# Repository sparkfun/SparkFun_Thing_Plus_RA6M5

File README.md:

SparkFun Thing Plus - RA6M5
========================================

[*SparkFun Thing Plus - RA6M5 (WRL-24243)*](https://www.sparkfun.com/products/24243)

Clocking in at 200MHz, the RA6M5 is a high-performance microcontroller from [Renesas](https://www.renesas.com/) that is perfect for real-time applications. The [SparkFun Thing Plus - RA6M5](https://www.sparkfun.com/products/24243), is our latest [Thing Plus board](https://www.sparkfun.com/thing_plus) featuring the standard Qwiic connector, JST LiPo battery connector, 21 GPIO pins broken out in a Feather footprint, and status indicator LEDs. At the core is the RA6M5 microcontroller, a low-power Arm^®^ Cortex^®^-M33 processor with an available 512kB of SRAM and 2MB of Flash and an extensive list of peripheral capabilities. Additionally, we have included 16MB of QSPI Flash and an SD card slot on the board, so users won't have to worry about running out of memory space or data storage options.

The SparkFun RA6M5 Thing Plus also features Bluetooth® Low Energy connectivity, thanks to the provided DA14531MOD module *(also from Renesas)*. When actively transmitting, the DA14531MOD sips a mere 4mA and is capable of operating from a small coin-cell battery. The firmware provided on the module features Renesas' [SmartBond™ - CodeLess™ AT command](https://lpccs-docs.renesas.com/UM-140-DA145x-CodeLess/index.html) set. Therefore, users only need to send AT commands to configure a Bluetooth connection; without the need to reprogram the module.

**Note:**

- While the Thing Plus - RA6M5 does include some 5V tolerant pins, it is primarily a **3.3V** *logic-level* board.
- While the full capabilities of the RA6M5 support a broad range of features, only a limited set may be implemented, by default, in the [Renesas-Arduino core](https://github.com/arduino/ArduinoCore-renesas). However, the capabilities of the Thing Plus - RA6M5 should be comparable to the [Arduino Portenta C33](https://store.arduino.cc/collections/portenta-family/products/portenta-c33); with the exclusion of WiFi connectivity.

Documentation
--------------

* **[Hookup Guide (mkdocs)](http://docs.sparkfun.com/SparkFun_Thing_Plus_RA6M5/)** - The hookup guide for the Thing Plus - RA6M5 hosted by GitHub pages.<br>
   
* [SparkFun Graphical Datasheets](https://github.com/sparkfun/Graphical_Datasheets) - Graphical Datasheets for various SparkFun products.

*Need to download or print our hookup guide?*

* [Print *(Print to PDF)* from Single-Page View](http://docs.sparkfun.com/SparkFun_Thing_Plus_RA6M5/print_view)

Repository Contents
-------------------

* **[/docs](/docs/)** - Online documentation files
    * [assets](/docs/assets/) - Assets files
        * [board_files](/docs/assets/board_files/) - Files for the product design
            * [Eagle design files](/docs/assets/board_files/eagle_files.zip) (.zip)
            * [Schematic](/docs/assets/board_files/schematic.pdf) (.pdf)
            * [Dimensions](/docs/assets/board_files/dimensions.pdf) (.pdf)
            * [Graphical Datasheet](/docs/assets/board_files/graphical_datasheet.pdf) (.pdf)
        * [component_documentation](/docs/assets/component_documentation/) - Datasheets for hardware components
        * [img/hookup_guide/](/docs/assets/img/hookup_guide/) - Images for hookup guide documentation
* **[/Hardware](/Hardware/)** - Eagle design files (.brd, .sch)
  * **[/Production](/Production/)** - Production files

Product Variants
----------------

* [WRL-24243](https://www.sparkfun.com/products/24243)- v1.0, Initial Release

Version History
---------------

* [v10](https://github.com/sparkfun/SparkFun_Thing_Plus_RA6M5/releases/tag/v10) - Initial Release

License Information
-------------------

This product is ***open source***!

Please review the [`LICENSE.md`](./LICENSE.md) file for license information.

If you have any questions or concerns about licensing, please contact technical support on our [SparkFun forums](https://forum.sparkfun.com/viewforum.php?f=152).

Distributed as-is; no warranty is given.

- Your friends at SparkFun.

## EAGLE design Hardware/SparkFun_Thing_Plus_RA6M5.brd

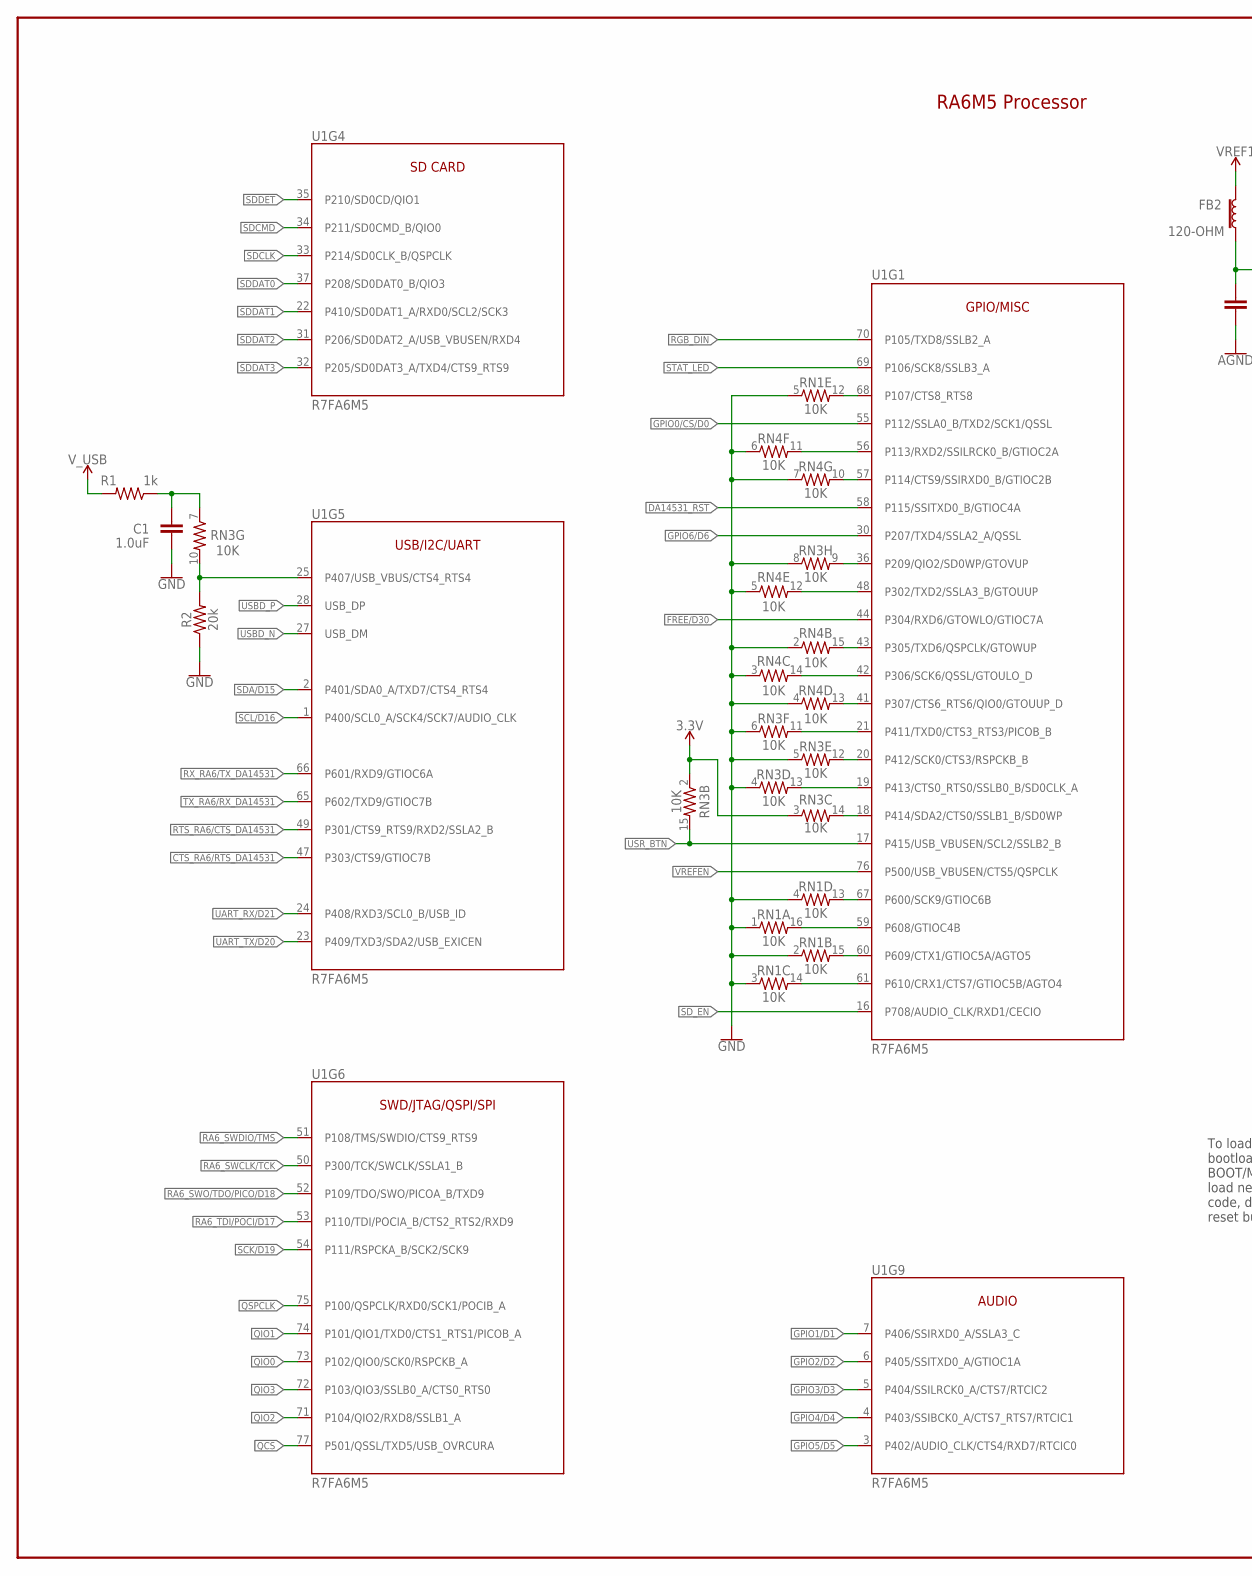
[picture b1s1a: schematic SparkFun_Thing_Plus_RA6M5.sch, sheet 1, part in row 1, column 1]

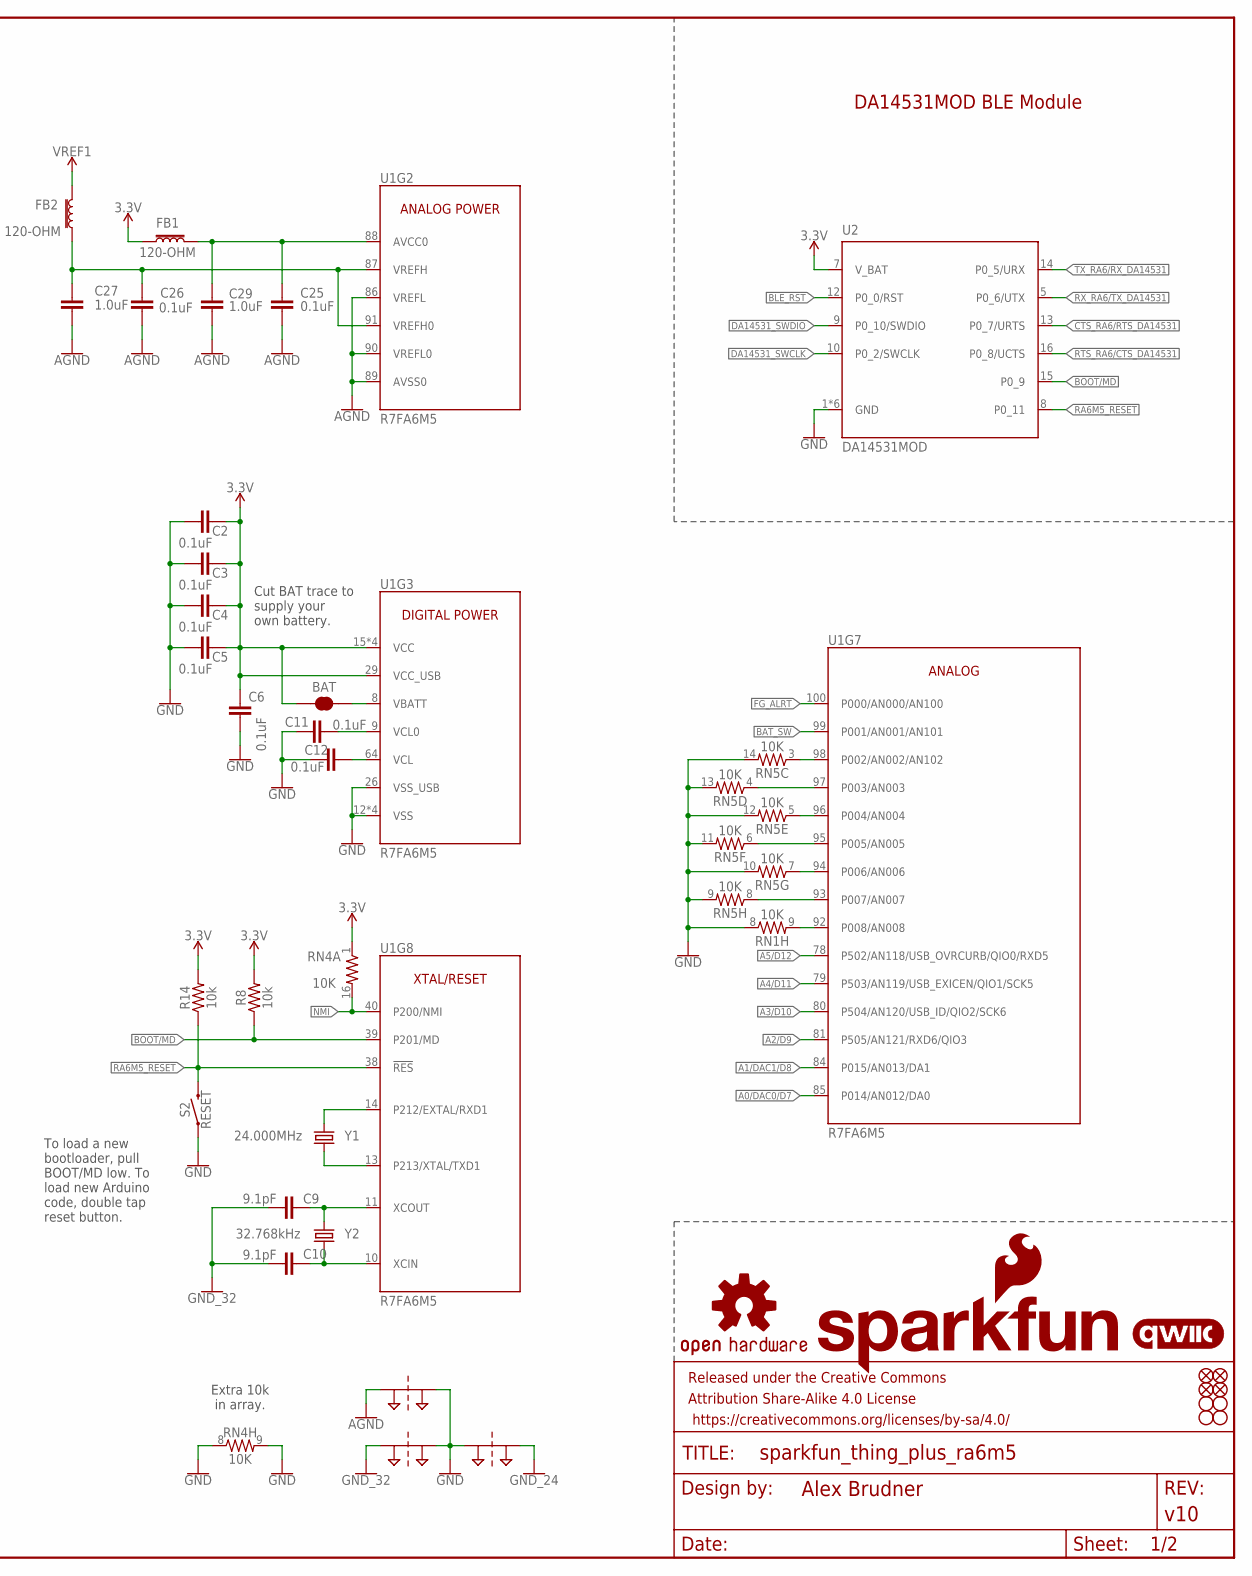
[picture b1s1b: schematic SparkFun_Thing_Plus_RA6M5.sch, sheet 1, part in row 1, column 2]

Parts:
BAT: JUMPER-SMT_2_NC_TRACE_SILK; SMT-JUMPER_2_NC_TRACE_SILK
C1, C27, C29: 1.0uF; 0402-TIGHT
C2, C3, C4, C5, C6, C11, C12, C25, C26: 0.1uF; 0402-TIGHT
C9, C10: 9.1pF; 0402-TIGHT
FB1, FB2: 120-OHM; 0402-TIGHT
FD1, FD2, FD3, FD4: FIDUCIALUFIDUCIAL; FIDUCIAL-MICRO
FRAME1: FRAME-LEDGER; CREATIVE_COMMONS
H1, H2, H3, H4: STAND-OFFTIGHT; STAND-OFF-TIGHT
LOGO1: OSHW-LOGOMINI; OSHW-LOGO-MINI
LOGO2: SFE_LOGO_NAME_FLAME.1_INCH; SFE_LOGO_NAME_FLAME_.1
LOGO3: QWIIC_LOGO_4MM; QWIIC_4MM
R1: 1k; 0402-TIGHT
R2: 20k; 0402-TIGHT
R8, R14: 10k; 0402-TIGHT
RN1, RN3, RN4, RN5: 10K; 2506_AR
S2: RESET; TACTILE_SWITCH_SMD_4.6X2.8MM
SUPPLYTIE1, SUPPLYTIE2, SUPPLYTIE3: 2PT_GND_TIESMALL; 2PT_GND_TIE_SMALL
U1: R7FA6M5; P-LQFP100-14X14-0.50
U2: DA14531MOD
Y1: 24.000MHz; 4-SMD,32X25
Y2: 32.768kHz; CRYSTAL-SMD-3.2X1.5MM

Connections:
3.3V: BAT.1, C2.1, C3.1, C4.1, C5.1, C6.1, FB1.1, R8.2, R14.2, RN3.2 (1), RN3.3 (1), RN4.1, U1.15 (VCC), U1.29 (VCC_USB), U1.46 (VCC), U1.62 (VCC), U1.82 (VCC), U2.7 (V_BAT); also elsewhere on the board
!CTS_RA6/RTS_DA14531!: U1.47 (P303/CTS9/GTIOC7B), U2.13 (P0_7/URTS); also elsewhere on the board
!DA14531_RST!: U1.58 (P115/SSITXD0_B/GTIOC4A); also elsewhere on the board
!FG_ALRT!: U1.100 (P000/AN000/AN100); also elsewhere on the board
!NMI!: RN4.16 (2), U1.40 (P200/NMI); also elsewhere on the board
!QCS!: U1.77 (P501/QSSL/TXD5/USB_OVRCURA); also elsewhere on the board
!RA6M5_RESET!: R14.1, S2.3 (2), S2.4 (2), U1.38 (!RES!), U2.8 (P0_11); also elsewhere on the board
!RTS_RA6/CTS_DA14531!: U1.49 (P301/CTS9_RTS9/RXD2/SSLA2_B), U2.16 (P0_8/UCTS); also elsewhere on the board
!SD_EN!: U1.16 (P708/AUDIO_CLK/RXD1/CECIO); also elsewhere on the board
!USR_BTN!: RN3.15 (2), U1.17 (P415/USB_VBUSEN/SCL2/SSLB2_B); also elsewhere on the board
A0/DAC0/D7: U1.85 (P014/AN012/DA0); also elsewhere on the board
A1/DAC1/D8: U1.84 (P015/AN013/DA1); also elsewhere on the board
A2/D9: U1.81 (P505/AN121/RXD6/QIO3); also elsewhere on the board
A3/D10: U1.80 (P504/AN120/USB_ID/QIO2/SCK6); also elsewhere on the board
A4/D11: U1.79 (P503/AN119/USB_EXICEN/QIO1/SCK5); also elsewhere on the board
A5/D12: U1.78 (P502/AN118/USB_OVRCURB/QIO0/RXD5); also elsewhere on the board
AGND: C25.2, C26.2, C27.2, C29.2, SUPPLYTIE1.P$1, U1.86 (VREFL), U1.89 (AVSS0), U1.90 (VREFL0)
AVCC0: C25.1, C29.1, FB1.2, U1.88 (AVCC0); also elsewhere on the board
BAT_SW: U1.99 (P001/AN001/AN101); also elsewhere on the board
BLE_RST: U2.12 (P0_0/RST); also elsewhere on the board
BOOT/MD: R8.1, U1.39 (P201/MD), U2.15 (P0_9); also elsewhere on the board
DA14531_SWCLK: U2.10 (P0_2/SWCLK); also elsewhere on the board
DA14531_SWDIO: U2.9 (P0_10/SWDIO); also elsewhere on the board
EXTAL: U1.14 (P212/EXTAL/RXD1), Y1.1
FREE/D30: U1.44 (P304/RXD6/GTOWLO/GTIOC7A); also elsewhere on the board
GND: C1.1, C2.2, C3.2, C4.2, C5.2, C6.2, C11.2, C12.2, R2.1, RN1.1, RN1.2 (1), RN1.3 (1), RN1.4 (1), RN1.5 (1), RN1.8 (1), RN3.4 (1), RN3.5 (1), RN3.6 (1), RN3.8 (1), RN4.2 (1), RN4.3 (1), RN4.4 (1), RN4.5 (1), RN4.6 (1), RN4.7 (1), RN4.8 (1), RN4.9 (2), RN5.9 (2), RN5.10 (2), RN5.11 (2), RN5.12 (2), RN5.13 (2), RN5.14 (2), S2.1, S2.2 (1), SUPPLYTIE1.P$2, SUPPLYTIE2.P$2, SUPPLYTIE3.P$1, U1.12 (VSS), U1.26 (VSS_USB), U1.45 (VSS), U1.63 (VSS), U1.83 (VSS), U2.1 (GND), U2.2 (GND), U2.3 (GND), U2.4 (GND), U2.6 (GND), U2.11 (GND); also elsewhere on the board
GND_24: SUPPLYTIE3.P$2
GND_32: C9.1, C10.1, SUPPLYTIE2.P$1
GPIO0/!CS!/D0: U1.55 (P112/SSLA0_B/TXD2/SCK1/QSSL); also elsewhere on the board
GPIO1/D1: U1.7 (P406/SSIRXD0_A/SSLA3_C); also elsewhere on the board
GPIO2/D2: U1.6 (P405/SSITXD0_A/GTIOC1A); also elsewhere on the board
GPIO3/D3: U1.5 (P404/SSILRCK0_A/CTS7/RTCIC2); also elsewhere on the board
GPIO4/D4: U1.4 (P403/SSIBCK0_A/CTS7_RTS7/RTCIC1); also elsewhere on the board
GPIO5/D5: U1.3 (P402/AUDIO_CLK/CTS4/RXD7/RTCIC0); also elsewhere on the board
GPIO6/D6: U1.30 (P207/TXD4/SSLA2_A/QSSL); also elsewhere on the board
unnamed: RN1.9 (2), U1.92 (P008/AN008)
unnamed: RN3.9 (2), U1.36 (P209/QIO2/SD0WP/GTOVUP)
unnamed: C1.2, R1.1, RN3.7 (1)
unnamed: RN3.14 (2), U1.18 (P414/SDA2/CTS0/SSLB1_B/SD0WP)
unnamed: R2.2, RN3.10 (2), U1.25 (P407/USB_VBUS/CTS4_RTS4)
unnamed: RN1.14 (2), U1.61 (P610/CRX1/CTS7/GTIOC5B/AGTO4)
unnamed: RN1.15 (2), U1.60 (P609/CTX1/GTIOC5A/AGTO5)
unnamed: RN1.16 (2), U1.59 (P608/GTIOC4B)
unnamed: RN4.15 (2), U1.43 (P305/TXD6/QSPCLK/GTOWUP)
unnamed: RN1.13 (2), U1.67 (P600/SCK9/GTIOC6B)
unnamed: RN3.13 (2), U1.19 (P413/CTS0_RTS0/SSLB0_B/SD0CLK_A)
unnamed: RN3.12 (2), U1.20 (P412/SCK0/CTS3/RSPCKB_B)
unnamed: RN3.11 (2), U1.21 (P411/TXD0/CTS3_RTS3/PICOB_B)
unnamed: C26.1, C27.1, FB2.1, U1.87 (VREFH), U1.91 (VREFH0)
unnamed: RN4.13 (2), U1.41 (P307/CTS6_RTS6/QIO0/GTOUUP_D)
unnamed: RN4.12 (2), U1.48 (P302/TXD2/SSLA3_B/GTOUUP)
unnamed: RN4.14 (2), U1.42 (P306/SCK6/QSSL/GTOULO_D)
unnamed: BAT.2, U1.8 (VBATT)
unnamed: RN4.10 (2), U1.57 (P114/CTS9/SSIRXD0_B/GTIOC2B)
unnamed: RN4.11 (2), U1.56 (P113/RXD2/SSILRCK0_B/GTIOC2A)
unnamed: RN1.12 (2), U1.68 (P107/CTS8_RTS8)
unnamed: RN5.8 (1), U1.93 (P007/AN007)
unnamed: RN5.7 (1), U1.94 (P006/AN006)
unnamed: RN5.6 (1), U1.95 (P005/AN005)
unnamed: RN5.5 (1), U1.96 (P004/AN004)
unnamed: RN5.4 (1), U1.97 (P003/AN003)
unnamed: RN5.3 (1), U1.98 (P002/AN002/AN102)
unnamed: C11.1, U1.9 (VCL0)
unnamed: C12.1, U1.64 (VCL)
QIO0: U1.73 (P102/QIO0/SCK0/RSPCKB_A); also elsewhere on the board
QIO1: U1.74 (P101/QIO1/TXD0/CTS1_RTS1/PICOB_A); also elsewhere on the board
QIO2: U1.71 (P104/QIO2/RXD8/SSLB1_A); also elsewhere on the board
QIO3: U1.72 (P103/QIO3/SSLB0_A/CTS0_RTS0); also elsewhere on the board
QSPCLK: U1.75 (P100/QSPCLK/RXD0/SCK1/POCIB_A); also elsewhere on the board
RA6_SWCLK/TCK: U1.50 (P300/TCK/SWCLK/SSLA1_B); also elsewhere on the board
RA6_SWDIO/TMS: U1.51 (P108/TMS/SWDIO/CTS9_RTS9); also elsewhere on the board
RA6_SWO/TDO/PICO/D18: U1.52 (P109/TDO/SWO/PICOA_B/TXD9); also elsewhere on the board
RA6_TDI/POCI/D17: U1.53 (P110/TDI/POCIA_B/CTS2_RTS2/RXD9); also elsewhere on the board
RGB_DIN: U1.70 (P105/TXD8/SSLB2_A); also elsewhere on the board
RX_RA6/TX_DA14531: U1.66 (P601/RXD9/GTIOC6A), U2.5 (P0_6/UTX); also elsewhere on the board
SCK/D19: U1.54 (P111/RSPCKA_B/SCK2/SCK9); also elsewhere on the board
SCL/D16: U1.1 (P400/SCL0_A/SCK4/SCK7/AUDIO_CLK); also elsewhere on the board
SDA/D15: U1.2 (P401/SDA0_A/TXD7/CTS4_RTS4); also elsewhere on the board
SDCLK: U1.33 (P214/SD0CLK_B/QSPCLK); also elsewhere on the board
SDCMD: U1.34 (P211/SD0CMD_B/QIO0); also elsewhere on the board
SDDAT0: U1.37 (P208/SD0DAT0_B/QIO3); also elsewhere on the board
SDDAT1: U1.22 (P410/SD0DAT1_A/RXD0/SCL2/SCK3); also elsewhere on the board
SDDAT2: U1.31 (P206/SD0DAT2_A/USB_VBUSEN/RXD4); also elsewhere on the board
SDDAT3: U1.32 (P205/SD0DAT3_A/TXD4/CTS9_RTS9); also elsewhere on the board
SDDET: U1.35 (P210/SD0CD/QIO1); also elsewhere on the board
STAT_LED: U1.69 (P106/SCK8/SSLB3_A); also elsewhere on the board
TX_RA6/RX_DA14531: U1.65 (P602/TXD9/GTIOC7B), U2.14 (P0_5/URX); also elsewhere on the board
UART_RX/D21: U1.24 (P408/RXD3/SCL0_B/USB_ID); also elsewhere on the board
UART_TX/D20: U1.23 (P409/TXD3/SDA2/USB_EXICEN); also elsewhere on the board
USBD_N: U1.27 (USB_DM); also elsewhere on the board
USBD_P: U1.28 (USB_DP); also elsewhere on the board
VREF1: FB2.2; also elsewhere on the board
VREFEN: U1.76 (P500/USB_VBUSEN/CTS5/QSPCLK); also elsewhere on the board
V_USB: R1.2; also elsewhere on the board
XCIN: C10.2, U1.10 (XCIN), Y2.P$1 (1)
XCOUT: C9.2, U1.11 (XCOUT), Y2.P$2 (2)
XTAL: U1.13 (P213/XTAL/TXD1), Y1.3 (2)

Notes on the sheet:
DA14531MOD BLE Module
RA6M5 Processor
Cut BAT trace to supply your own battery.
Extra 10k in array.
To load a new bootloader, pull BOOT/MD low. To load new Arduino code, double tap reset button.

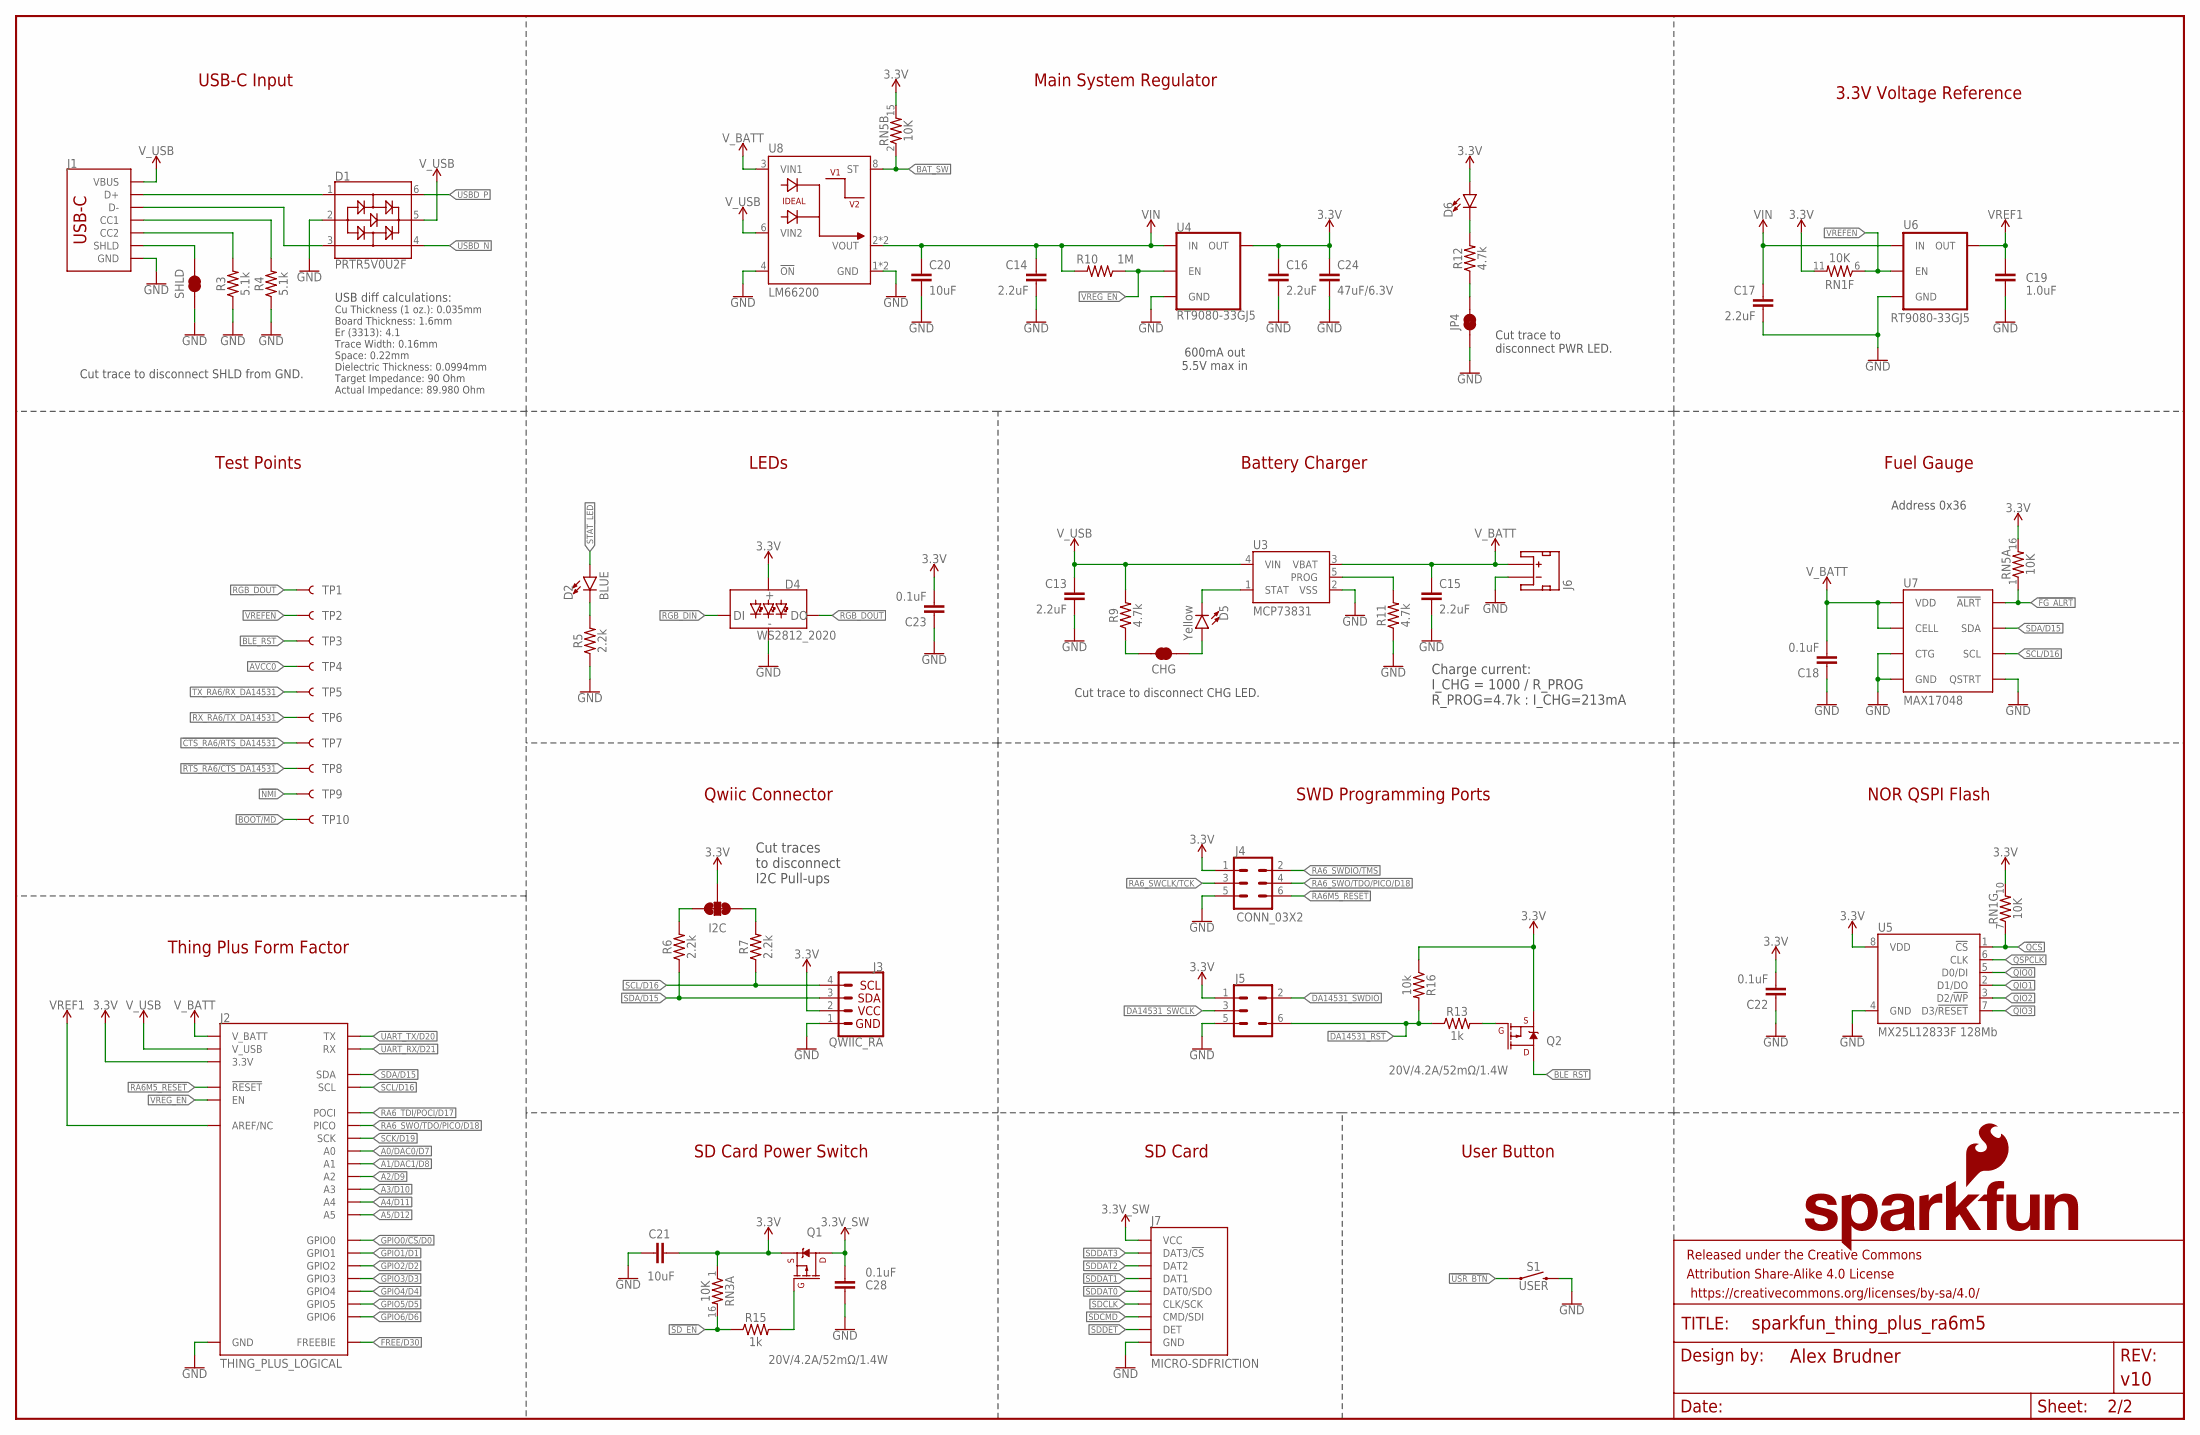
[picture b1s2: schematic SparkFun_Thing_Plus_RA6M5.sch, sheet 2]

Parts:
C13, C14, C15, C16, C17: 2.2uF; 0402-TIGHT
C18, C22, C23, C28: 0.1uF; 0402-TIGHT
C19: 1.0uF; 0402-TIGHT
C20, C21: 10uF; 0805
C24: 47uF/6.3V; 0805
CHG: JUMPER-SMT_2_NC_TRACE_SILK; SMT-JUMPER_2_NC_TRACE_SILK
D1: PRTR5V0U2F; SOT886
D2: BLUE; LED-0603
D4: WS2812_2020; WS2812-2020
D5: Yellow; LED-0603
D6: LED-RED_0603-KB; LED-0603
FRAME2: FRAME-LEDGERNO_FOOTPRINT; DUMMY
I2C: JUMPER-SMT_3_2-NC_TRACE_SILK; SMT-JUMPER_3_2-NC_TRACE_SILK
J1: USB Female Type C Connector; USB-C-16P-6LAYER-ISOLATED
J2: THING_PLUS_LOGICAL; THING_PLUS
J3: QWIIC_RA; JST04_1MM_RA
J4: CONN_03X2; PAD_05_03X2_TP
J5: SWD-5PIN; PAD_05_03X2_TP_NO4
J6: JST_2MM_MALE; JST-2-SMD
J7: MICRO-SDFRICTION; MICROSD_TINY
JP4: JUMPER-SMT_2_NC_TRACE_SILK; SMT-JUMPER_2_NC_TRACE_SILK
LOGO4: SFE_LOGO_NAME_FLAMEBLANK; BLANK
Q1, Q2: 20V/4.2A/52mΩ/1.4W; SOT23-3
R3, R4: 5.1k; 0402-TIGHT
R5, R6, R7: 2.2k; 0402-TIGHT
R9, R11, R12: 4.7k; 0402-TIGHT
R10: 1M; 0402-TIGHT
R13, R15: 1k; 0402-TIGHT
R16: 10k; 0402-TIGHT
RN1, RN3, RN5: 10K; 2506_AR
S1: USER; TACTILE_SWITCH_SMD_4.6X2.8MM
SHLD: JUMPER-SMT_2_NC_TRACE_SILK; SMT-JUMPER_2_NC_TRACE_SILK
TP1, TP3, TP5, TP6, TP7, TP8, TP10: TEST-POINT3X5; PAD.03X.05
TP2: TEST-POINT3X4; PAD.03X.04
TP4, TP9: TEST-POINT3; PAD.03X.03
U3: MCP73831; SOT23-5
U4, U6: RT9080-33GJ5; SOT23-5
U5: MX25L12833F 128Mb; WSON-8-6X5
U7: MAX17048; DFN-8
U8: LM66200; SOT8

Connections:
3.3V: C16.1, C21.1, C22.2, C23.2, C24.1, D4.VCC, D6.A, I2C.2, J2.27 (3.3V), J3.2, J4.1, J5.1, Q1.2 (S), Q2.2 (S), R16.1, RN1.10 (2), RN1.11 (2), RN3.1, RN5.15 (2), RN5.16 (2), U4.5 (OUT), U5.8 (VDD); also elsewhere on the board
3.3V_SW: C28.2, J7.4 (VCC), Q1.3 (D)
!CTS_RA6/RTS_DA14531!: TP7.1; also elsewhere on the board
!DA14531_RST!: J5.6, R13.1, R16.2; also elsewhere on the board
!FG_ALRT!: RN5.1, U7.5 (!ALRT); also elsewhere on the board
!NMI!: TP9.1; also elsewhere on the board
!QCS!: RN1.7 (1), U5.1 (!CS!); also elsewhere on the board
!RA6M5_RESET!: J2.28 (!RESET), J4.6; also elsewhere on the board
!RTS_RA6/CTS_DA14531!: TP8.1; also elsewhere on the board
!SD_EN!: R15.1, RN3.16 (2); also elsewhere on the board
!USR_BTN!: S1.1, S1.2 (1); also elsewhere on the board
A0/DAC0/D7: J2.24 (A0); also elsewhere on the board
A1/DAC1/D8: J2.23 (A1); also elsewhere on the board
A2/D9: J2.22 (A2); also elsewhere on the board
A3/D10: J2.21 (A3); also elsewhere on the board
A4/D11: J2.20 (A4); also elsewhere on the board
A5/D12: J2.19 (A5); also elsewhere on the board
AVCC0: TP4.1; also elsewhere on the board
BAT_SW: RN5.2 (1), U8.8 (ST); also elsewhere on the board
BLE_RST: Q2.3 (D), TP3.1; also elsewhere on the board
BOOT/MD: TP10.1; also elsewhere on the board
DA14531_SWCLK: J5.3; also elsewhere on the board
DA14531_SWDIO: J5.2; also elsewhere on the board
FREE/D30: J2.13 (FREEBIE); also elsewhere on the board
GND: C13.2, C14.2, C15.2, C16.2, C17.2, C18.1, C19.2, C20.2, C21.2, C22.1, C23.1, C24.2, C28.1, D1.2, D4.GND, J1.GND, J1.GND2 (GND), J2.25 (GND), J3.1, J4.5, J5.5, J6.1 (-), J7.6 (GND), J7.GND1 (GND), J7.GND2 (GND), J7.GND3 (GND), J7.GND4 (GND), J7.GND5 (GND), J7.GND6 (GND), JP4.1, R3.1, R4.1, R5.1, R11.1, S1.3 (2), S1.4 (2), SHLD.1, U3.2 (VSS), U4.2 (GND), U5.4 (GND), U6.2 (GND), U7.1 (CTG), U7.4 (GND), U7.6 (QSTRT), U7.9 (GND), U8.1 (GND), U8.4 (!ON!), U8.5 (GND); also elsewhere on the board
GPIO0/!CS!/D0: J2.9 (GPIO0); also elsewhere on the board
GPIO1/D1: J2.8 (GPIO1); also elsewhere on the board
GPIO2/D2: J2.7 (GPIO2); also elsewhere on the board
GPIO3/D3: J2.6 (GPIO3); also elsewhere on the board
GPIO4/D4: J2.5 (GPIO4); also elsewhere on the board
GPIO5/D5: J2.4 (GPIO5); also elsewhere on the board
GPIO6/D6: J2.3 (GPIO6); also elsewhere on the board
unnamed: CHG.2, R9.1
unnamed: CHG.1, D5.A
unnamed: D5.C, U3.1 (STAT)
unnamed: Q2.1 (G), R13.2
unnamed: R11.2, U3.5 (PROG)
unnamed: D2.C, R5.2
unnamed: I2C.1, R6.2
unnamed: I2C.3, R7.2
unnamed: JP4.2, R12.1
unnamed: D6.C, R12.2
unnamed: J1.SHLD1 (SHLD), J1.SHLD2 (SHLD), J1.SHLD3 (SHLD), J1.SHLD4 (SHLD), J1.SHLD5 (SHLD), J1.SHLD6 (SHLD), J1.SHLD7 (SHLD), J1.SHLD8 (SHLD), SHLD.2
unnamed: J1.B5 (CC2), R3.2
unnamed: J1.A5 (CC1), R4.2
unnamed: Q1.1 (G), R15.2
QIO0: U5.5 (D0/DI); also elsewhere on the board
QIO1: U5.2 (D1/DO); also elsewhere on the board
QIO2: U5.3 (D2/!WP!); also elsewhere on the board
QIO3: U5.7 (D3/!RESET!); also elsewhere on the board
QSPCLK: U5.6 (CLK); also elsewhere on the board
RA6_SWCLK/TCK: J4.3; also elsewhere on the board
RA6_SWDIO/TMS: J4.2; also elsewhere on the board
RA6_SWO/TDO/PICO/D18: J2.17 (PICO), J4.4; also elsewhere on the board
RA6_TDI/POCI/D17: J2.16 (POCI); also elsewhere on the board
RGB_DIN: D4.DI; also elsewhere on the board
RGB_DOUT: D4.DO, TP1.1
RX_RA6/TX_DA14531: TP6.1; also elsewhere on the board
SCK/D19: J2.18 (SCK); also elsewhere on the board
SCL/D16: J2.2 (SCL), J3.4, R7.1, U7.7 (SCL); also elsewhere on the board
SDA/D15: J2.1 (SDA), J3.3, R6.1, U7.8 (SDA); also elsewhere on the board
SDCLK: J7.5 (CLK/SCK); also elsewhere on the board
SDCMD: J7.3 (CMD/SDI); also elsewhere on the board
SDDAT0: J7.7 (DAT0/SDO); also elsewhere on the board
SDDAT1: J7.8 (DAT1); also elsewhere on the board
SDDAT2: J7.1 (DAT2); also elsewhere on the board
SDDAT3: J7.2 (DAT3/!CS!); also elsewhere on the board
SDDET: J7.9 (DET); also elsewhere on the board
STAT_LED: D2.A; also elsewhere on the board
TX_RA6/RX_DA14531: TP5.1; also elsewhere on the board
UART_RX/D21: J2.15 (RX); also elsewhere on the board
UART_TX/D20: J2.14 (TX); also elsewhere on the board
USBD_N: D1.4; also elsewhere on the board
USBD_P: D1.6; also elsewhere on the board
USBIN_N: D1.3, J1.A7 (D-), J1.B7 (D-)
USBIN_P: D1.1, J1.A6 (D+), J1.B6 (D+)
VIN: C14.1, C17.1, C20.1, R10.2, U4.1 (IN), U6.1 (IN), U8.2 (VOUT), U8.7 (VOUT)
VREF1: C19.1, J2.26 (AREF/NC), U6.5 (OUT); also elsewhere on the board
VREFEN: RN1.6 (1), TP2.1, U6.3 (EN); also elsewhere on the board
VREG_EN: J2.11 (EN), R10.1, U4.3 (EN)
V_BATT: C15.1, C18.2, J2.12 (V_BATT), J6.2 (+), U3.3 (VBAT), U7.2 (CELL), U7.3 (VDD), U8.3 (VIN1)
V_USB: C13.1, D1.5, J1.VBUS1 (VBUS), J1.VBUS2 (VBUS), J2.10 (V_USB), R9.2, U3.4 (VIN), U8.6 (VIN2); also elsewhere on the board

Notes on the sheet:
USB-C Input
Main System Regulator
Battery Charger
Test Points
3.3V Voltage Reference
Fuel Gauge
NOR QSPI Flash
SWD Programming Ports
Qwiic Connector
LEDs
Thing Plus Form Factor
SD Card
Cut trace to disconnect PWR LED.
Cut trace to disconnect CHG LED.
Cut trace to disconnect SHLD from GND.
Cut traces to disconnect I2C Pull-ups
Charge current: I_CHG = 1000 / R_PROG R_PROG=4.7k : I_CHG=213mA
600mA out 5.5V max in
SD Card Power Switch
USB diff calculations:
Cu Thickness (1 oz.): 0.035mm Board Thickness: 1.6mm Er (3313): 4.1 Trace Width: 0.16mm Space: 0.22mm Dielectric Thickness: 0.0994mm Target Impedance: 90 Ohm Actual Impedance: 89.980 Ohm
Address 0x36
User Button

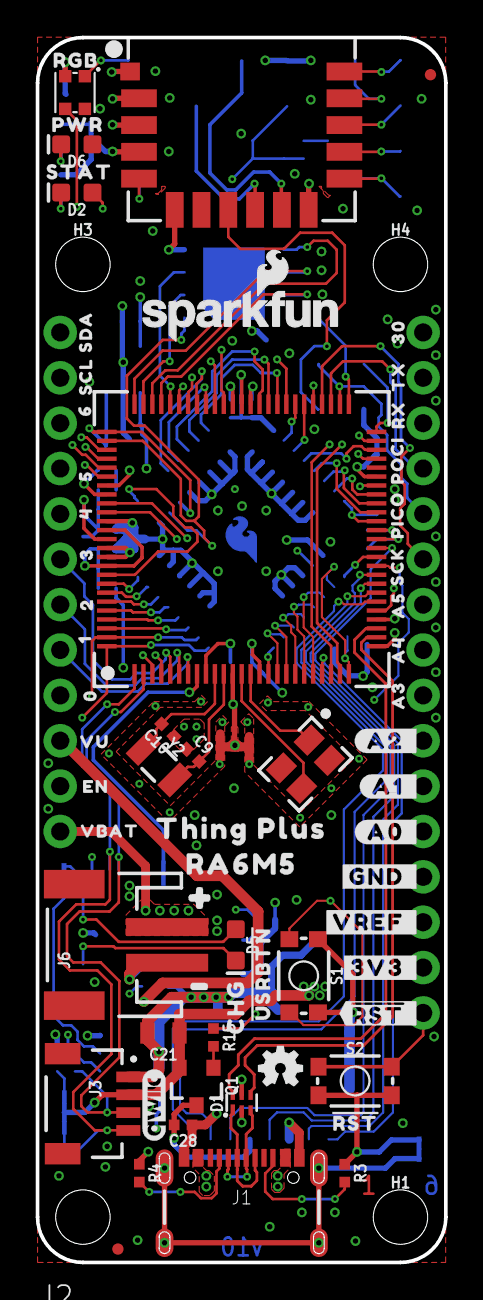
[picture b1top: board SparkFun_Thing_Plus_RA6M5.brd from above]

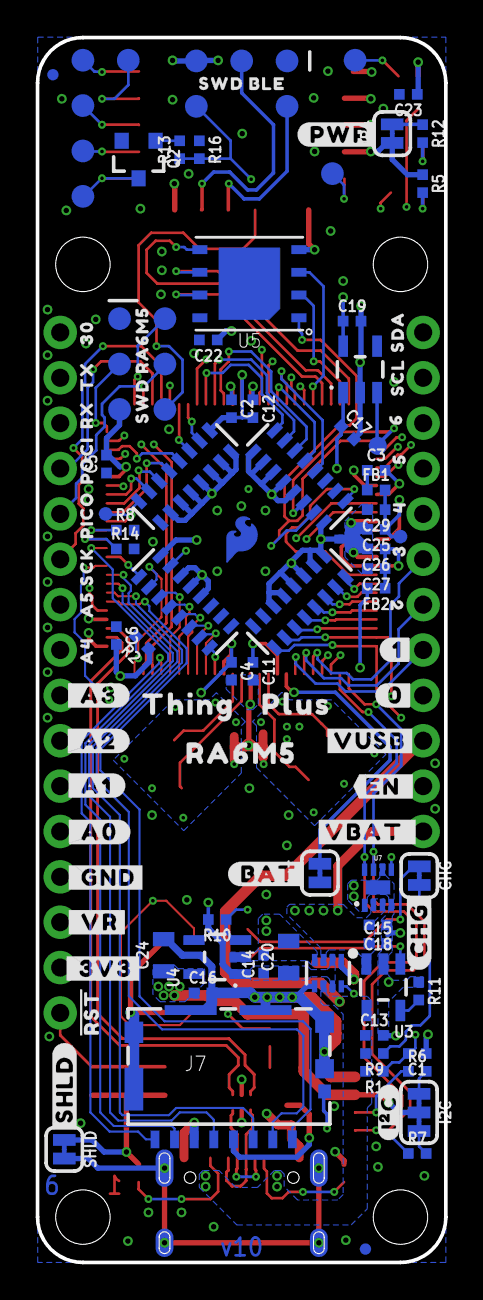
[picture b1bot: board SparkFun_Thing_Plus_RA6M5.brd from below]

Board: 6 copper layers, 22.9 x 68.6 mm, 185 parts (109 on the bottom side), 117 nets.

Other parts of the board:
U$3: #I�C#0
U$4: #CHG#0
U$8: SFE_LOGO_FLAME_COPPER_EXPOSED_.1
U$9: SWD_RA6M50
U$10: SWD_BLE0
U$12, U$86: 300
U$13, U$51: #RST#0
U$14: CHG0
U$15: STAT0
U$16: PWR0
U$17: RGB0
U$18: THING_PLUS0
U$19: ##RST#_#0
U$20: #3V3_#0
U$21: #VREF_#0
U$22: #GND_#0
U$23: #A0_#0
U$24: #A1_#0
U$25: #A2_#0
U$26: A30
U$27, U$59: A40
U$28, U$60: A50
U$29, U$61: SCK0
U$30, U$62: PICO0
U$31, U$63: POCI0
U$32, U$64: RX0
U$33, U$65: TX0
U$34, U$43: 60
U$35, U$67: SDA0
U$36, U$68: SCL0
U$37, U$48: 50
U$38, U$66: 40
U$39, U$69: 30
U$40, U$70: 20
U$41: 10
U$42: 00
U$44: VU0
U$45: EN0
U$46: VBAT0
U$47: #PWR#0
U$49: #BAT#0
U$50: #SHLD#0
U$52: #_3V3#0
U$53: #_VR#0
U$54: #_GND#0
U$55: #_A0#0
U$56: #_A1#0
U$57: #_A2#0
U$58: #_A3#0
U$71: #1#0
U$72: #0#0
U$73: #USRBTN#0
U$76: #VUSB#0
U$77: #EN_#0
U$78: #VBAT_#0
U$79, U$82: RA6M50
U$80: ORDERING_INSTRUCTIONS
U$81: #0
U$83: THING0
U$84: PLUS0
U$85: _#0

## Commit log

2023-11-07 Schematic complete.
    Board mostly has components laid out.
2023-11-07 Update Test Points, ready for v01 schematic review
2023-11-07 Add documentation, update xtal caps.
2023-11-08 test 6L
2023-11-08 Made board 6L and created 6L Isolated USB
2023-11-08 Added LM66200 and incorporated it.
2023-11-10 update based on pre-design review comments.
2023-12-07 Update Sch, Lbr, & Brd files.
    Add broken out resistors for boot/reset pins.
    Move array resistors around to make them route easier.
    Add BAT jumper.
    Add 1u to AVCC net.
    Move spare array resistor to bottom.
    Pull status pin to 3.3V for LM66200.
2023-12-07 Update SparkFun_Thing_Plus_RA6M5.lbr
    Add missing Prod_ID.
2023-12-07 Add gerbers for v01.
2023-12-13 Post design review, pre-design review changes.
2023-12-15 Add LM66200 Datasheet.
2023-12-15 Update post-design review.
    Add USB diff calcs to schematic.
    Add product name silk to bottom of board.
    Consolidate 0.1u caps.
    Stitch power and ground planes better.
    Analyze PDN to chip and improve.
    Pour 3V3 under USB on top and bot.
2023-12-19 Add panel for v01.
2023-12-19 Move to prod folder
2023-12-21 Minor update to v01.
    Add Fuel Gauge address text to schematic.
    Add +/- silk for battery connector.
    Re-export PDF.
2024-02-13 Add tests. All but QSPI and BLE working.
2024-02-14 Use Serial2.
2024-02-26 Add Codeless BLE basic wrapper. Add examples, test. Add arduino library files. Add gitignore. Add license.
2024-02-26 Update for Reds.
    Change QSPI flash chip to same one as Portenta C33
    Remove boot button
    Move reset button to space it out
    Add boot test point
    Recenter programming header silk
    Update GPIO silk
2024-02-26 Add 6-board panel files.
2024-02-29 Add CodelessBLE zip for arduino.
2024-02-29 Add QSPI Datasheet
2024-02-29 fix parsePipeData bug
2024-02-29 V10 hardware post reds review update
    Connect fills on bottom side near bottom diamond.
    Add user button near reset button.
    VREF EN now pulls up to 3.3V instead of VIN.
    Change VREF silk bottom side to inverted VA.
    Update EN and !RST! silk flags to use the right arrow.
    Move vias to allow fills.
2024-02-29 Rename silk
    VA to VR.
2024-02-29 Remove unused default folders.
2024-02-29 Repanelize post reds review.
2024-03-08 Update LICENSE.md
    Remove carriage returns
    Fix grammar
2024-03-08 Datasheets
    Move files into new directory
    Added datasheets for peripheral components
2024-03-08 Initial documentation setup
2024-03-19 Update Codeless Firmware. Update library.properties with correct URL. Add comments and header to examples. Remove unused code in examples. Remove magic numbers in examples and libraries. Comment code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
2024-03-19 Update examples. Refactor examples to use new function names. Rezip library post changes.
2024-03-19 Remove WIP binary mode code.
2024-03-20 Update SD test to remove SD power control.
2024-04-06 Move datasheet
2024-04-06 Add hardware documents
2024-04-06 Update GitHub information
2024-04-06 Initial Documentation Commit
2024-04-06 Ported Renesas-Arduino Core
2024-04-09 Update video links
    Update product video link and QR code
    Add QR code for Qwiic connect system video
2024-04-09 Add alt text
2024-04-09 Fix Copy/Paste
    Remove instances of ESP32 or mosaic-X5 (copy/paste errors)
2024-04-09 Update documentation
2024-04-09 Update SFE-Renesas-Arduino_core.zip
    Update Arduino Core for bootloader
2024-04-09 Create CodelessBLE.zip
    Add CodeLess Arduino library
2024-04-09 Enable automatic GitHub Pages build/deployment
2024-04-09 Link CodeLess library file
2024-04-12 Update SFE-Renesas-Arduino_core.zip
    Replace linkers in FATFileSystems with required files
2024-04-12 Update documentation
    Update instructions for FastLED library and Arduino core
    Few other corrections
2024-04-12 Fix Abbreviations
    Disabled the CSS on the permalink icon that was causing the issue
2024-04-12 Add link to Eagle Files
2024-04-12 Snippets Rework
    Reworked snippets - multiple base paths
    - Removes need for ./docs/ for snippets to code in docs folder
    - Removes need for ../ for snippets to code outside of the docs folder (i.e. root directory)
2024-04-12 Update SD card information
    Remove commented out library
    Added warnings and file system information
2024-04-12 Update programming information
2024-04-12 Add DFU information
2024-04-12 Update README.md
    Fix typo
2024-04-12 Fix header spacing
    Fixes issue with abbreviation and permalink in header
2024-04-12 Add Examples
    Examples for the digital and analog functionality
2024-04-12 Update software_overview-arduino.md
    Use snippets
2024-04-12 Update hardware_overview.md
    Clean up - Remove indentation
2024-04-12 Update example-digital.md
    Remove indentation
2024-04-12 Add SPI and Serial Examples
2024-04-12 Update mkdocs.yml
    Restore original order of plugins... affects build
2024-04-15 Remove permalink CSS
    Removes formatting issues in headers... caused by the styling for permalinks
    - The flex positioning caused superscript and subscript text to be centered
2024-04-15 Update documentation
    Adds examples for I2C, SD card, flash memory, and DA14531MOD
2024-04-15 Update graphical_datasheet.pdf
    Fix digital pin labeled for user button
2024-04-15 Update/Add Examples
    Include BME688 for SPI, I2C, and BLE examples
2024-04-15 Fix indentations
2024-04-28 Rename file
    Typo on filename
2024-04-28 Fix grammar
    Fix grammatical issue
2024-04-28 Update resources.md
    Add QR code for printouts
2024-04-28 Create favicon.ico
    For DuckDuckGo browser compatibility
    - The browser submits multiple file requests, each time the webpage is reloaded
2024-04-28 Add file exclusions
    Adding a configuration for file exclusions during builds (and when utilizing the development server). This should alleviate a few of errors during the webpage build process.
2024-05-17 Update tutorial thumbnail
2024-05-17 Update example-codeless.md
    Update link to command set
2024-05-17 Add new CSS styling for video
    Testing a new CSS implementation for the video containers
    - Should auto-size to a maximum width (defaulted with 500px)
2024-05-30 Highlight specific board definition
2024-05-30 Update software_overview-arduino.md
    Update instructions in response to: https://github.com/sparkfun/SparkFun_Thing_Plus_RA6M5/issues/5
2024-05-30 Update example-codeless.md
    Fix typo
2024-05-30 Update logo
    Only, single file needed
    Renamed file
2024-05-30 Update mkdocs.yml
    Disables plugins on local builds (no longer need to comment/uncomment blocks)
2024-05-30 Update mkdocs.yml
    Add files to build
    Move glossary on list
2024-05-30 Deployed 44e53fc with MkDocs version: 1.6.0
2024-08-06 Update mkdocs.yml
    Fix indentation
2024-08-06 Backup old Arduino Core
    Backup of original Arduino Core
2024-08-06 Update SFE-Renesas-Arduino_core.zip
    Add support for C33 variant
2024-08-06 Update software_overview-arduino.md
    Restores default instructions for FastLED library (pull request was merged)
2024-08-06 Update LICENSE.md
    Add Markdown formatting to make it more readable on GitHub
2024-08-06 Deployed 5b97d75 with MkDocs version: 1.6.0
2026-06-03 Deployed bd0d9c3 with MkDocs version: 1.6.1
2026-06-03 Remove center tag
2026-06-03 Fix MathJax and KaTeX
2026-06-03 Remove git-authors plug-in
2026-06-03 Update workflow
2026-06-03 Deployed f24808e with MkDocs version: 1.6.1
2026-06-03 Fix badge
2026-06-03 Deployed cb40655 with MkDocs version: 1.6.1
2026-06-03 Deployed b655d23 with MkDocs version: 1.6.1

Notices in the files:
parts and their libraries:
SparkFun-Aesthetics: Licensing: Creative Commons ShareAlike 4.0 International - https://creativecommons.org/licenses/by-sa/4.0
SparkFun-Aesthetics: Released under the Creative Commons Attribution Share-Alike 4.0 License
SparkFun-Aesthetics: https://creativecommons.org/licenses/by-sa/4.0
